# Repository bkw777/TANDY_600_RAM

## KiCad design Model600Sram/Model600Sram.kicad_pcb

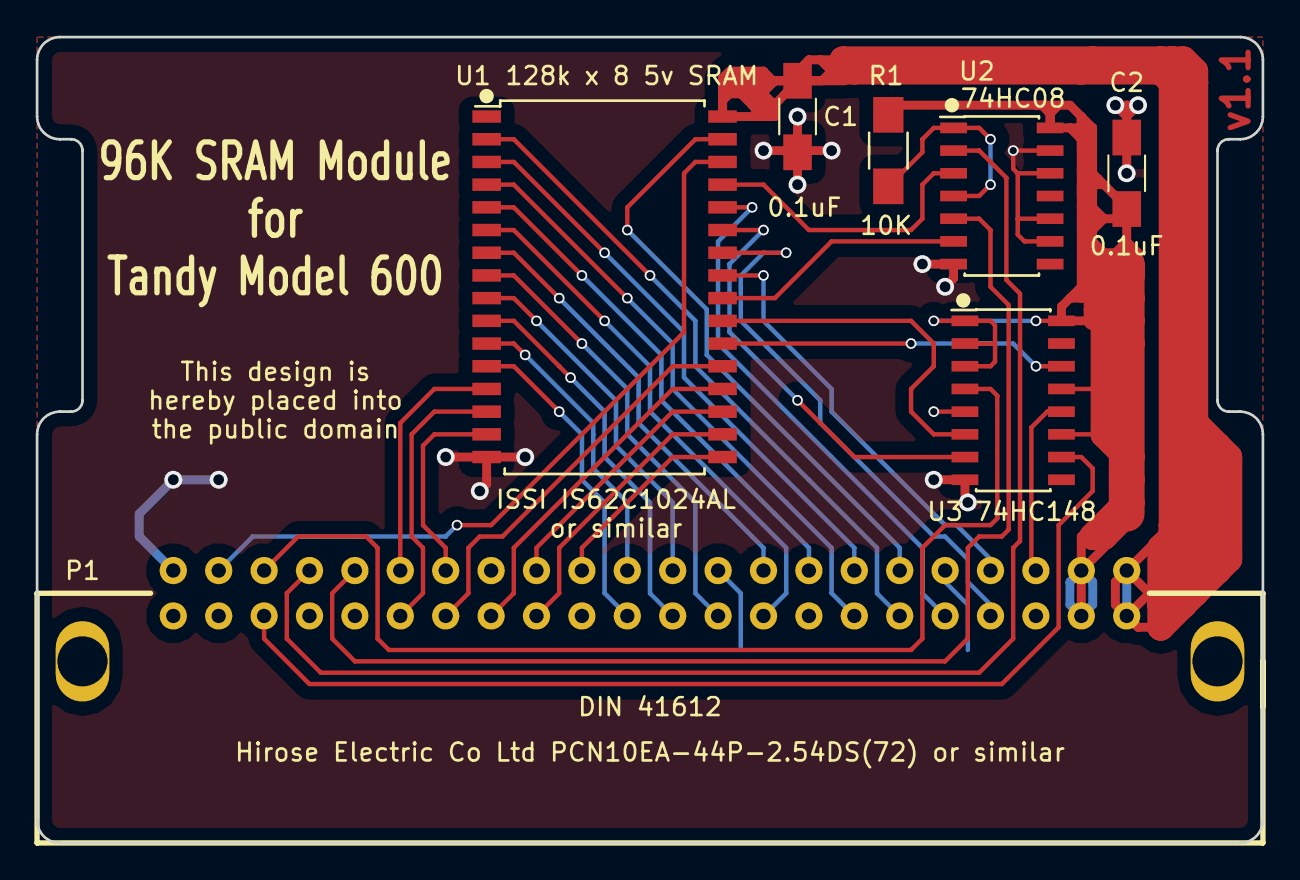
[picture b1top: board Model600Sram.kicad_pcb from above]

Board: 2 copper layers, 68.6 x 45.1 mm, 7 parts (0 on the bottom side), 38 nets.

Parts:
C1, C2: 0.1uF; C_1206_HandSoldering
P1: DIN 41612; DIN41612-44-RightAngle
R1: 10K; R_1206_HandSoldering
U1: 128k x 8 5v SRAM; SOP32-WIDE
U2: 74HC08; SOIC-14_3.9x8.7mm_Pitch1.27mm
U3: 74HC148; SOIC-16_3.9x9.9mm_Pitch1.27mm

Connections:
/A0: P1.24, U1.11
/A1: P1.23, U1.12
/A2: P1.22, U1.9
/A3: P1.21, U1.10
/A4: P1.19, U1.8
/A5: P1.18, U1.7
/A6: P1.17, U1.6
/A7: P1.16, U1.5
/A8: P1.14, U1.3
/A9: P1.13, U1.4
/A10: P1.12, U1.31
/A11: P1.11, U1.2
/A12: P1.9, U1.28
/A13: P1.8, U1.25
/A14: P1.7, U1.26
/A15: U1.27, U3.7
/A16: U1.23, U3.6
/CS1: U1.22, U3.14
/CS2: P1.42, U1.30
/D0: P1.34, U1.13
/D1: P1.33, U1.14
/D2: P1.32, U1.15
/D3: P1.31, U1.21
/D4: P1.29, U1.20
/D5: P1.28, U1.19
/D6: P1.27, U1.18
/D7: P1.26, U1.17
/PU: R1.2, U2.1, U2.4
/~CS1~_Bank0: P1.6, U3.12
/~CS1~_Bank1: P1.40, U3.4
/~CS1~_Bank2: P1.39, U3.10
/~OE: P1.36, U2.5
/~OE~_Gated: U1.24, U2.6
/~WE: P1.38, U2.2
/~WE~_Gated: U1.29, U2.3
GND: C1.2, C2.2, P1.5, P1.10, P1.15, P1.20, P1.25, P1.35, P1.37, P1.43, P1.44, U1.16, U2.7, U2.9, U2.10, U2.12, U2.13, U3.5, U3.8
VCC: C2.1, P1.3, P1.4, R1.1, U2.14, U3.1, U3.2, U3.3, U3.11, U3.13, U3.16
VMEM: C1.1, P1.1, P1.2, U1.32

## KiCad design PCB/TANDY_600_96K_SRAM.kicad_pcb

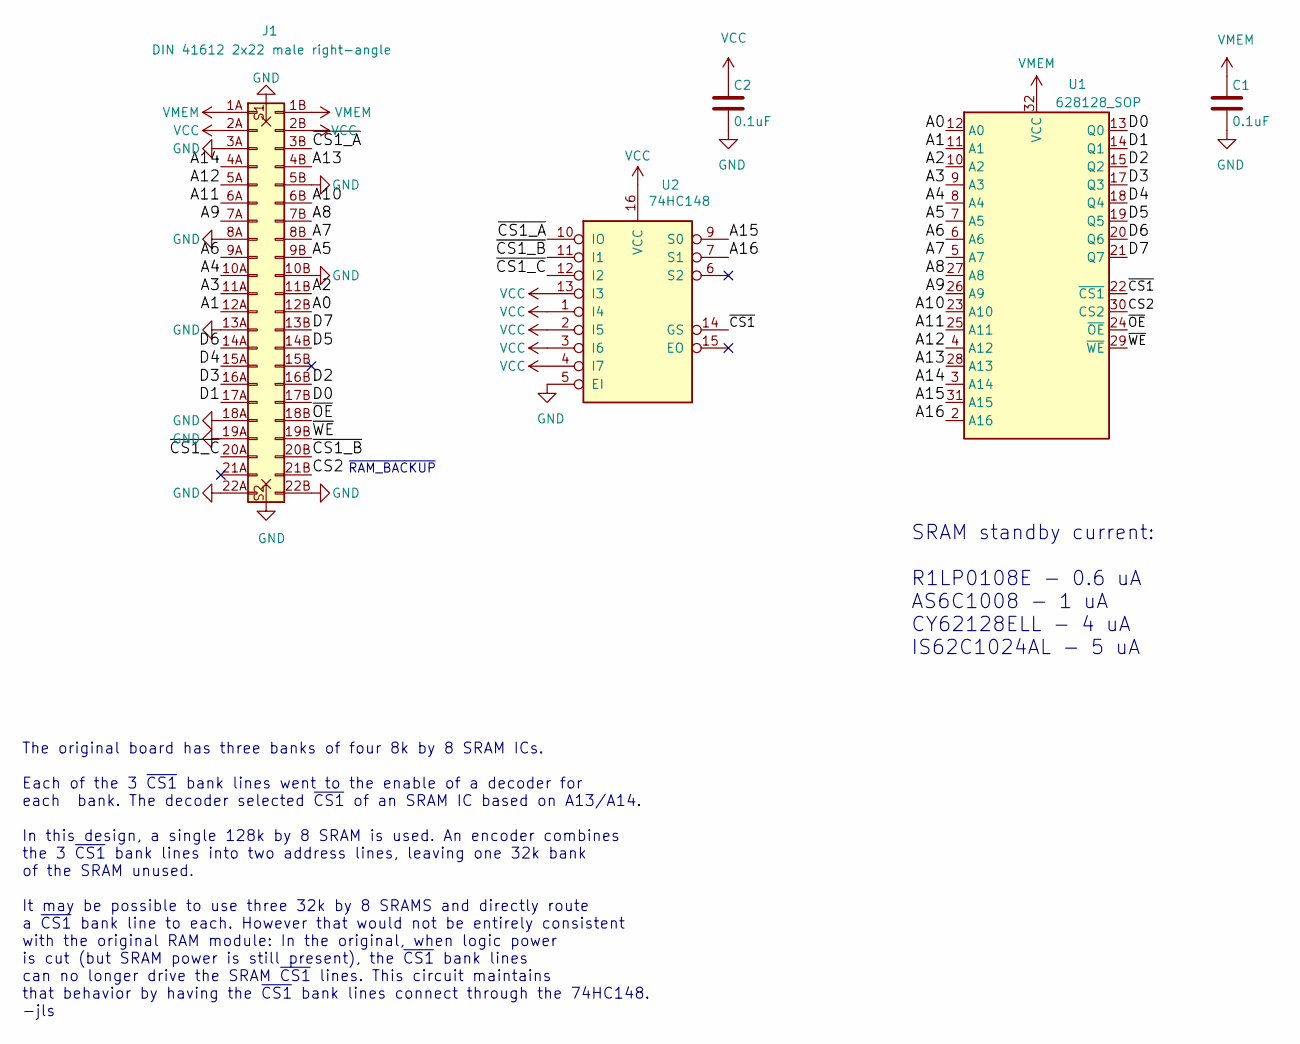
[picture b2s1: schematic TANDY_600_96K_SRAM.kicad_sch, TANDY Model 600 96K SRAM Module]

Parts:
C1, C2: 0.1uF; C_1206
J1: DIN 41612 2x22 male right-angle
U1: 628128_SOP; SOP-32W
U2: 74HC148; SOIC-SOP-16

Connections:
/A0: J1.12B, U1.12 (A0)
/A1: J1.12A, U1.11 (A1)
/A2: J1.11B, U1.10 (A2)
/A3: J1.11A, U1.9 (A3)
/A4: J1.10A, U1.8 (A4)
/A5: J1.9B, U1.7 (A5)
/A6: J1.9A, U1.6 (A6)
/A7: J1.8B, U1.5 (A7)
/A8: J1.7B, U1.27 (A8)
/A9: J1.7A, U1.26 (A9)
/A10: J1.6B, U1.23 (A10)
/A11: J1.6A, U1.25 (A11)
/A12: J1.5A, U1.4 (A12)
/A13: J1.4B, U1.28 (A13)
/A14: J1.4A, U1.3 (A14)
/A15: U1.31 (A15), U2.9 (S0)
/A16: U1.2 (A16), U2.7 (S1)
/CS2: J1.21B, U1.30 (CS2)
/D0: J1.17B, U1.13 (Q0)
/D1: J1.17A, U1.14 (Q1)
/D2: J1.16B, U1.15 (Q2)
/D3: J1.16A, U1.17 (Q3)
/D4: J1.15A, U1.18 (Q4)
/D5: J1.14B, U1.19 (Q5)
/D6: J1.14A, U1.20 (Q6)
/D7: J1.13B, U1.21 (Q7)
/~CS1_A: J1.3B, U2.10 (IO)
/~CS1_B: J1.20B, U2.11 (I1)
/~CS1_C: J1.20A, U2.12 (I2)
/~CS1: U1.22 (~CS1), U2.14 (GS)
/~OE: J1.18B, U1.24 (~OE)
/~WE: J1.19B, U1.29 (~WE)
GND: C1.2, C2.2, J1.3A, J1.5B, J1.8A, J1.10B, J1.13A, J1.18A, J1.19A, J1.22A, J1.22B, J1.S1 (mount), J1.S2 (mount), U1.16 (GND), U2.5 (EI), U2.8 (GND)
VCC: C2.1, J1.2A, J1.2B, U2.1 (I4), U2.2 (I5), U2.3 (I6), U2.4 (I7), U2.13 (I3), U2.16 (VCC)
VMEM: C1.1, J1.1A, J1.1B, U1.32 (VCC)

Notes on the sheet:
~{RAM_BACKUP}
SRAM standby current: R1LP0108E - 0.6 uA AS6C1008 - 1 uA CY62128ELL - 4 uA IS62C1024AL - 5 uA
The original board has three banks of four 8k by 8 SRAM ICs. Each of the 3 ~{CS1} bank lines went to the enable of a decoder for each bank. The decoder selected ~{CS1} of an SRAM IC based on A13/A14. In this design, a single 128k by 8 SRAM is used. An encoder combines the 3 ~{CS1} bank lines into t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

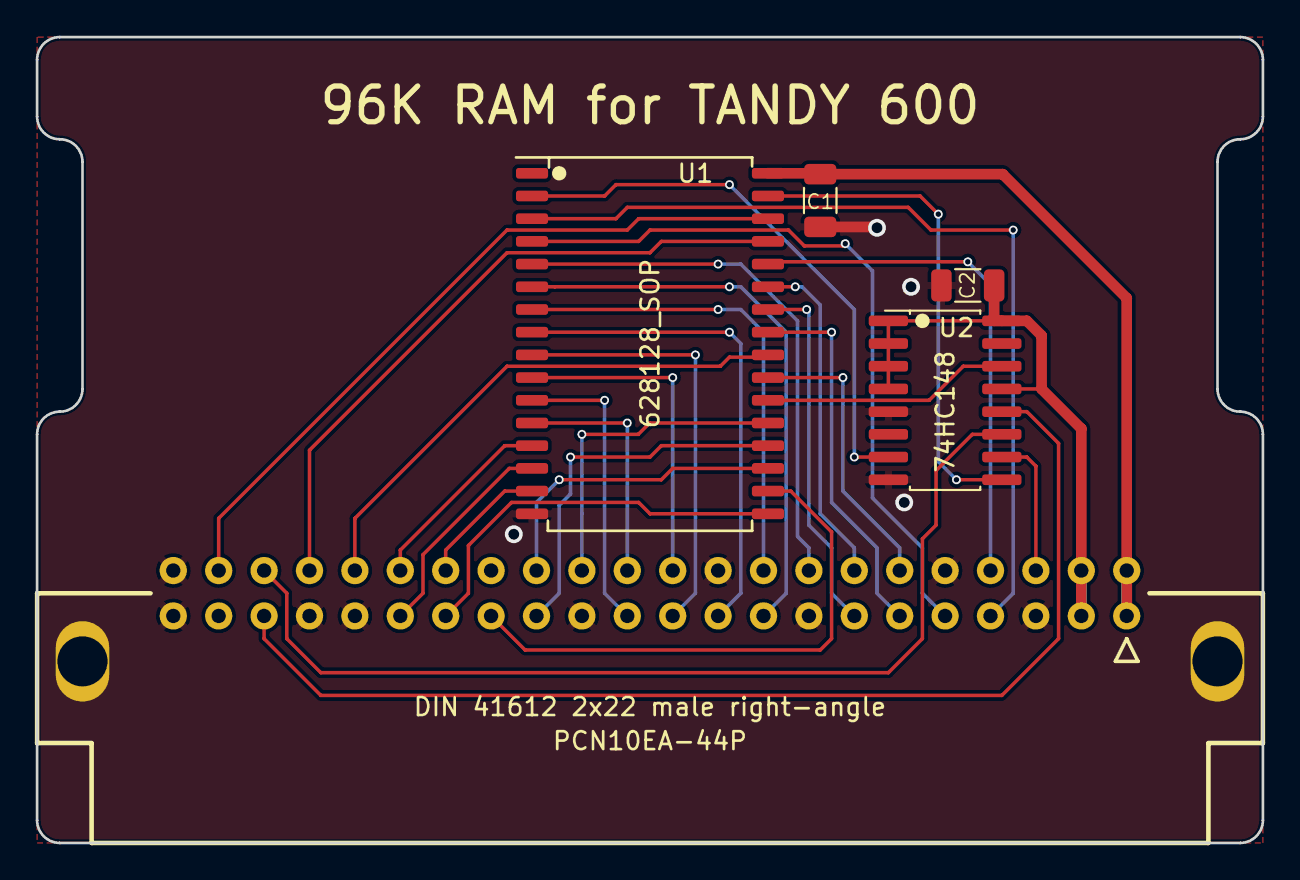
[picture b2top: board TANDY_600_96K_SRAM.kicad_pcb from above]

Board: 2 copper layers, 68.6 x 45.1 mm, 5 parts (0 on the bottom side), 35 nets.

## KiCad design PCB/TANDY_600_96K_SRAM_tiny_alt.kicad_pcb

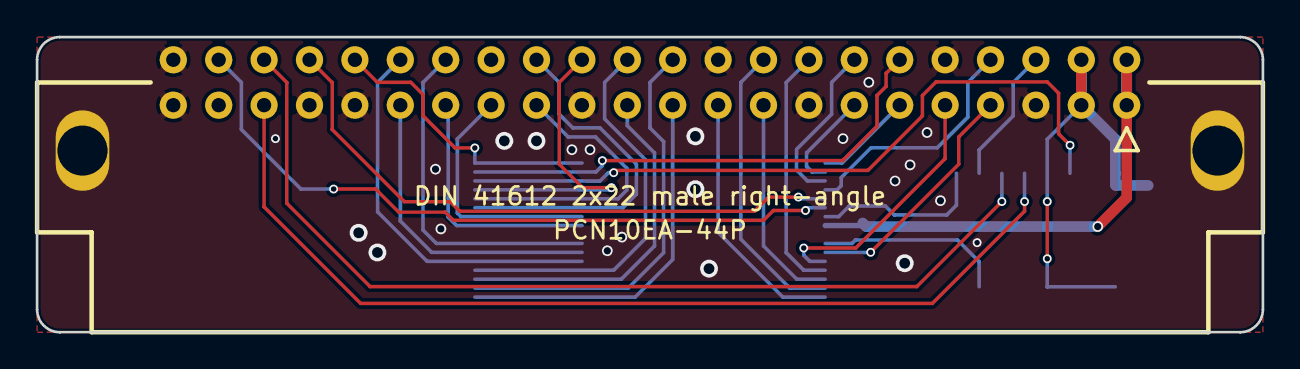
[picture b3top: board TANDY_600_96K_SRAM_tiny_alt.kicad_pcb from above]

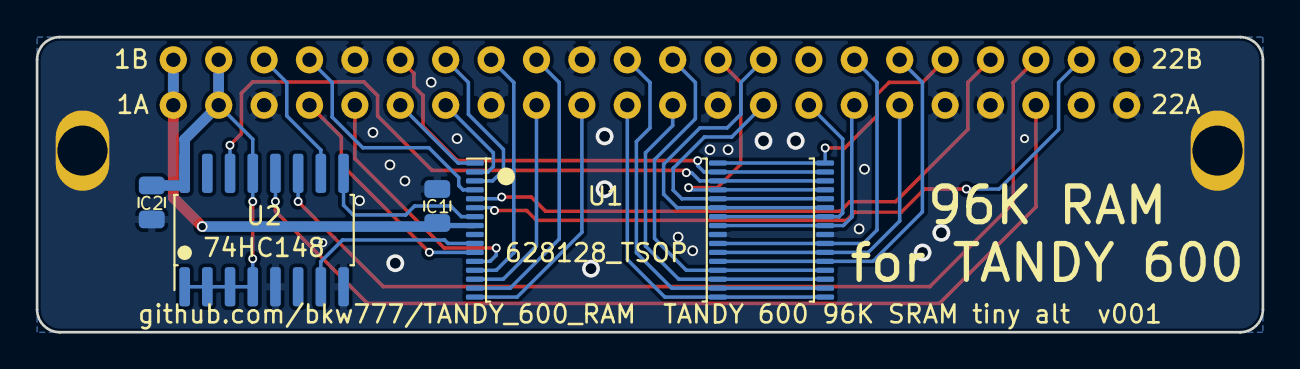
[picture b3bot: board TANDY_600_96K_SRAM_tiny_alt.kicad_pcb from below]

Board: 2 copper layers, 68.6 x 16.5 mm, 5 parts (4 on the bottom side), 35 nets.

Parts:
C1, C2: 0.1uF; C_0805
J1: DIN 41612 2x22 male right-angle
U1: 628128_TSOP; TSOP32-dual
U2: 74HC148; SOIC-SOP-16

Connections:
/A0: J1.12B, U1.20 (A0)
/A1: J1.12A, U1.19 (A1)
/A2: J1.11B, U1.18 (A2)
/A3: J1.11A, U1.17 (A3)
/A4: J1.10A, U1.16 (A4)
/A5: J1.9B, U1.15 (A5)
/A6: J1.9A, U1.14 (A6)
/A7: J1.8B, U1.13 (A7)
/A8: J1.7B, U1.3 (A8)
/A9: J1.7A, U1.2 (A9)
/A10: J1.6B, U1.31 (A10)
/A11: J1.6A, U1.1 (A11)
/A12: J1.5A, U1.12 (A12)
/A13: J1.4B, U1.4 (A13)
/A14: J1.4A, U1.11 (A14)
/A15: U1.7 (A15), U2.9 (S0)
/A16: U1.10 (A16), U2.7 (S1)
/CS2: J1.21B, U1.6 (CS2)
/D0: J1.17B, U1.21 (Q0)
/D1: J1.17A, U1.22 (Q1)
/D2: J1.16B, U1.23 (Q2)
/D3: J1.16A, U1.25 (Q3)
/D4: J1.15A, U1.26 (Q4)
/D5: J1.14B, U1.27 (Q5)
/D6: J1.14A, U1.28 (Q6)
/D7: J1.13B, U1.29 (Q7)
/~CS1_A: J1.3B, U2.10 (IO)
/~CS1_B: J1.20B, U2.11 (I1)
/~CS1_C: J1.20A, U2.12 (I2)
/~CS1: U1.30 (~CS1), U2.14 (GS)
/~OE: J1.18B, U1.32 (~OE)
/~WE: J1.19B, U1.5 (~WE)
GND: C1.2, C2.2, J1.3A, J1.5B, J1.8A, J1.10B, J1.13A, J1.18A, J1.19A, J1.22A, J1.22B, J1.S1 (mount), J1.S2 (mount), U1.24 (GND), U2.5 (EI), U2.8 (GND)
VCC: C2.1, J1.2A, J1.2B, U2.1 (I4), U2.2 (I5), U2.3 (I6), U2.4 (I7), U2.13 (I3), U2.16 (VCC)
VMEM: C1.1, J1.1A, J1.1B, U1.8 (VCC)

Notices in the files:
Model600Sram/Model600Sram.kicad_pcb:
the public domain
PCB/TANDY_600_96K_SRAM.kicad_pcb:
LICENSE: CC-BY-SA 4.0
